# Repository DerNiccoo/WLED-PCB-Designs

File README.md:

# WLED-PCB-Designs
Collection of my WLED PCB Controllers and Boards. They are not perfect, they are not the best, but I tried.

Main Constraints are 1oz copper with 2 layer and 100x100 maximum size to still get the cheap PCB manufacture prices.

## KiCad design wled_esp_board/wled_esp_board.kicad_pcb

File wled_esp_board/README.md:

# WLED ESP32-S3 Controller Board

A compact, low-idle-power ESP32-S3 development board designed as a drop-in controller for WLED-driven LED installations. The board accepts both 5V via pin headers and USB-C (USB 2.0), exposes the full ESP32-S3 GPIO pinout on standard 2.54 mm headers, and deliberately omits an LDO regulator in favor of a switching buck converter to minimize idle power draw.

## Overview

This board was created because I wanted to create my own dev board with the focus on low power consumption even in idle.

## Motivation & Design Decisions

- **Buck converter instead of LDO**: The AP63203WU is a 2A synchronous step-down regulator. Compared to a classic AMS1117/ME6211-style LDO, it wastes virtually no power as heat at light loads, making it ideal for always-on WLED setups.
- **USB-C (USB 2.0, 16-pin)**: Full USB-C receptacle with proper CC resistors (R2/R3, 5.1 kΩ) for correct 5V/500mA enumeration and ESD protection via USBLC6-2SC6.
- **Schottky reverse-polarity diode (D1, SS34)**: Protects the board when power is fed through the 5V pin headers. 3A continuous rating with low forward voltage to minimize drop.
- **Polyfuse (F1)**: Resettable 1A/30V PTC fuse on the USB path for short-circuit protection — no need to replace fuses after a mishap.
- **Reset + Boot buttons**: Physical access to BOOT and RESET for easy firmware flashing without needing any external tool.
- **Easy iron solderable**: 5 small 1mm pins to access as better access to solder the backside of the ESP without the need of a heatgun or hotplate

## Pinout

The board breaks out all ESP32-S3-WROOM-1 GPIOs across four 9-pin 2.54 mm headers (J1–J4). Power rails (5V and 3.3V) are available directly on the headers.

## Schematic

## PCB Layout

***

## Bill of Materials

> LCSC links point to the exact parts used. Where no LCSC link is listed, the part is a generic 0805 passive available from any supplier.

| Ref | Qty | Value / Part | Package | Key Specs | LCSC |
|-----|-----|-------------|---------|-----------|------|
| U1 | 1 | ESP32-S3-WROOM-1 | SMD 25.5×18 mm | Xtensa LX7 dual-core, 2.4 GHz Wi-Fi + BT5, 16 MB flash, 8 MB PSRAM | [C2913202](https://www.lcsc.com/product-detail/C2913202.html) |
| U2 | 1 | USBLC6-2SC6 | SOT-23-6 | ESD protection, 17V clamp, 5A Ipp — guards USB-C data lines | [C7519](https://www.lcsc.com/product-detail/C7519.html) |
| U3 | 1 | AP63203WU | TSOT-23-6 | 2A sync buck, 3.3V fixed output, 1.1 MHz, no LDO heat waste | [C780769](https://www.lcsc.com/product-detail/C780769.html) |
| L1 | 1 | 4.7 µH | 1210 | 2.5A / 3.1A saturation, 115 mΩ DCR — buck converter output inductor | [C48945753](https://www.lcsc.com/product-detail/C48945753.html) |
| D1 | 1 | SS34 | SMA (DO-214AC) | 40V / 3A Schottky, reverse-polarity protection on 5V pin rail | [C8678](https://www.lcsc.com/product-detail/C8678.html) |
| F1 | 1 | Polyfuse 1A | 1206 | PTC resettable fuse 30V / 1A — USB input overcurrent protection | [C5358568](https://www.lcsc.com/product-detail/C5358568.html) |
| J2 | 1 | USB-C Receptacle | HRO TYPE-C-31-M-12 | USB 2.0, 16-pin, through-hole reinforced | — |
| J1,J3,J4,J5 | 4 | 1×9 Pin Header | 2.54 mm | GPIO breakout headers | [C41430882](https://www.lcsc.com/product-detail/C41430882.html) |
| C1,C3,C6,C9 | 4 | 100 nF | 0805 | Decoupling caps for power rails | — |
| C2,C7,C8 | 3 | 22 µF | 0805 | Bulk capacitance, X5R ceramic 6.3V | [C307530](https://www.lcsc.com/product-detail/C307530.html) |
| C5 | 1 | 10 µF | 0805 | Buck output filter capacitor | — |
| R1 | 1 | 10 kΩ | 0805 | Pull-up resistor | — |
| R2,R3 | 2 | 5.1 kΩ | 0805 | USB-C CC pull-down resistors (required for correct 5V/500mA enumeration) | — |
| R4,R5 | 2 | 22 Ω | 0805 | USB D+/D− series termination resistors | — |
| SW1 | 1 | Reset | 5.2×5.2 mm SMD tact | Hardware reset | — |
| SW2 | 1 | Boot | 5.2×5.2 mm SMD tact | Puts ESP32-S3 into download mode | — |

***

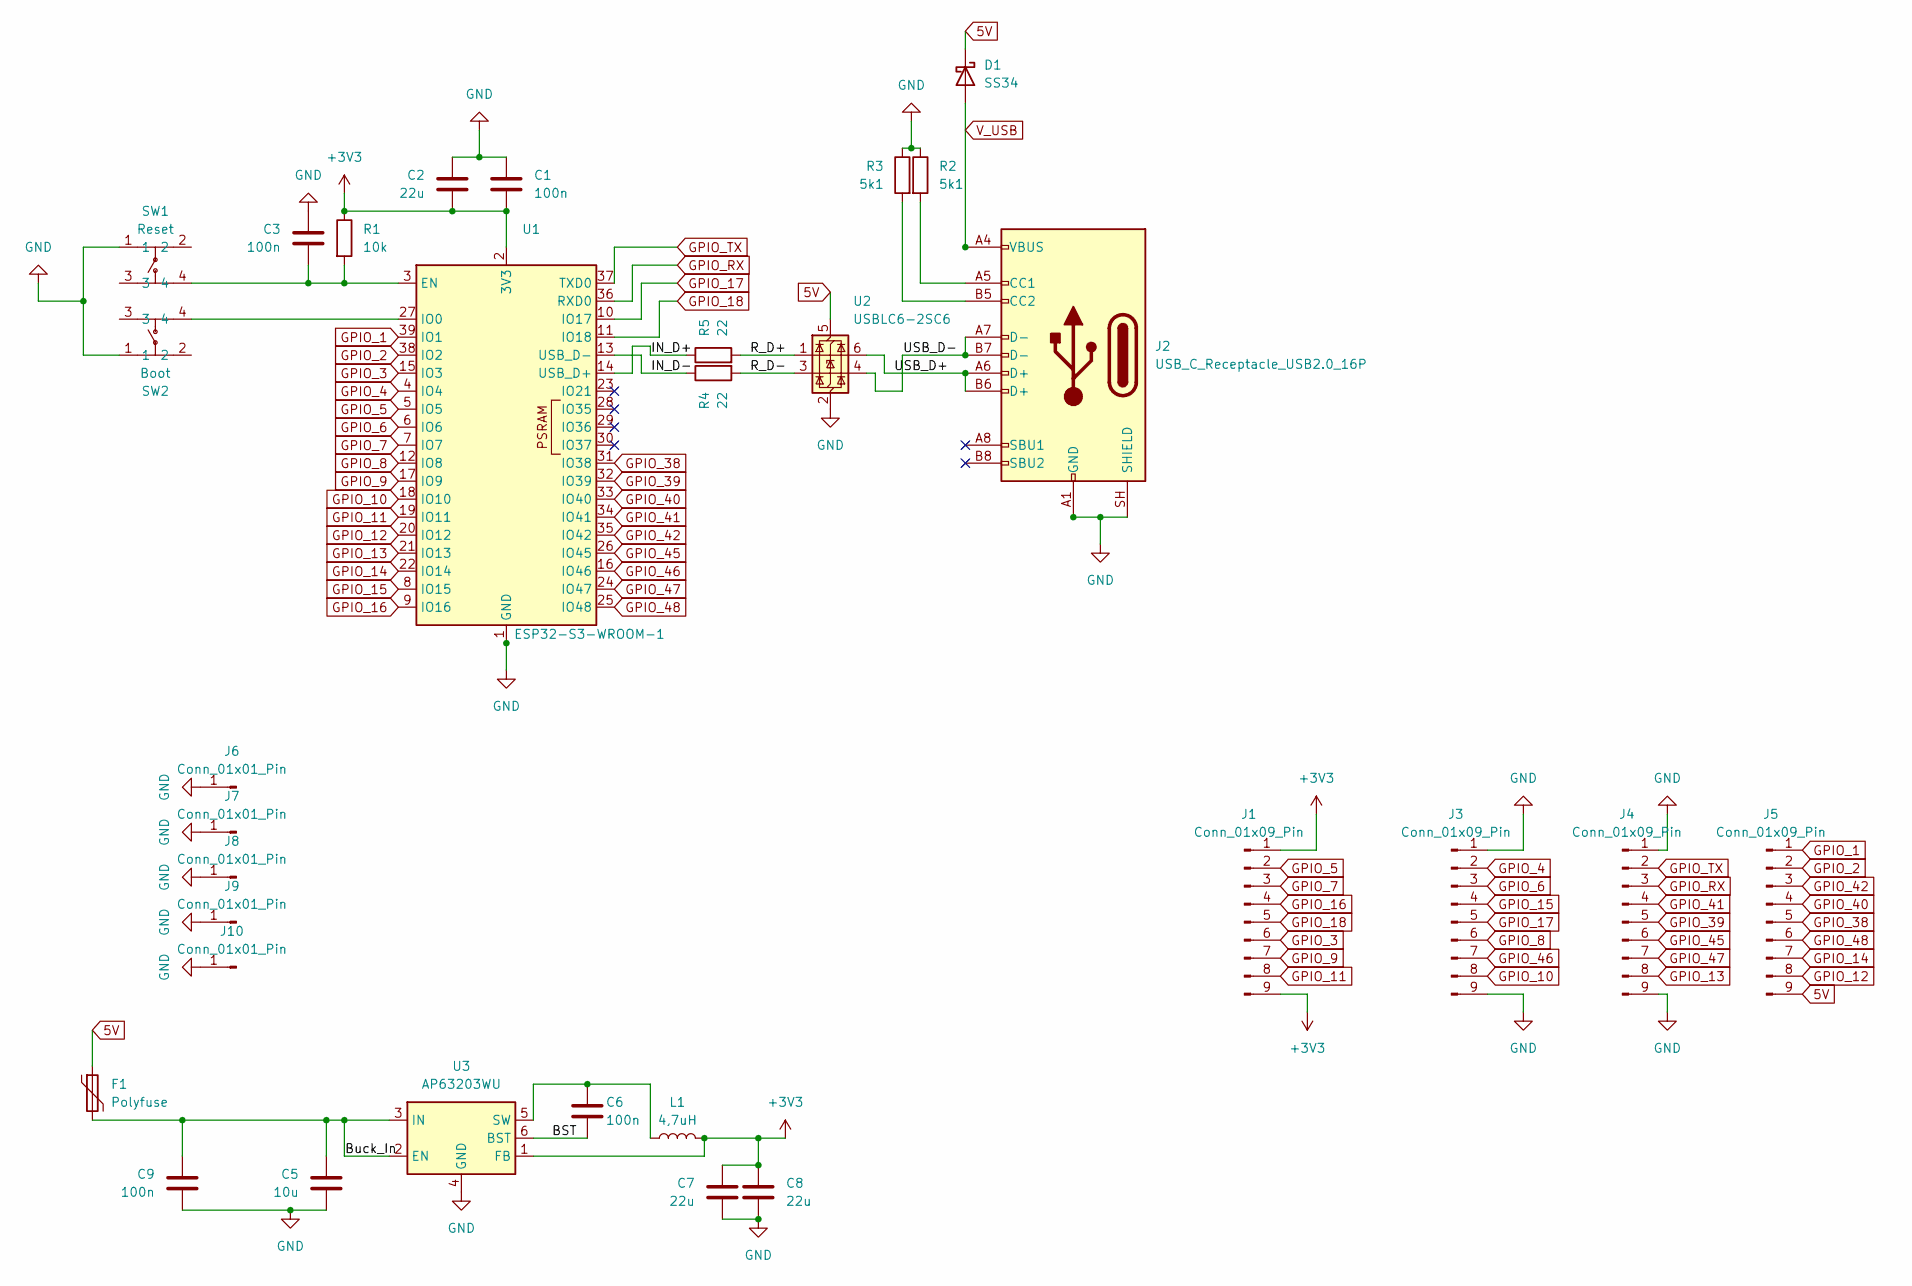
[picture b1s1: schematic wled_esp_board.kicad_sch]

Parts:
C1, C3, C6, C9: 100n; C_0805_2012Metric_Pad1.18x1.45mm_HandSolder
C2, C7, C8: 22u; C_0805_2012Metric_Pad1.18x1.45mm_HandSolder
C5: 10u; C_0805_2012Metric_Pad1.18x1.45mm_HandSolder
D1: SS34; D_SMA_Handsoldering
F1: Polyfuse; Fuse_1206_3216Metric_Pad1.42x1.75mm_HandSolder
J1, J3, J4, J5: Conn_01x09_Pin; PinHeader_1x09_P2.54mm_Vertical
J2: USB_C_Receptacle_USB2.0_16P; USB_C_Receptacle_HRO_TYPE-C-31-M-12
J6, J7, J8, J9, J10: Conn_01x01_Pin; PinHeader_1x01_P1.00mm_Horizontal
L1: 4,7uH; L_1210_3225Metric_Pad1.42x2.65mm_HandSolder
R1: 10k; R_0805_2012Metric_Pad1.20x1.40mm_HandSolder
R2, R3: 5k1; R_0805_2012Metric_Pad1.20x1.40mm_HandSolder
R4, R5: 22; R_0805_2012Metric_Pad1.20x1.40mm_HandSolder
SW1: Reset; SW-SMD_4P-L5.2-W5.2-P3.70-LS6.4; LCSC Part C36936641
SW2: Boot; SW-SMD_4P-L5.2-W5.2-P3.70-LS6.4; LCSC Part C36936641
U1: ESP32-S3-WROOM-1
U2: USBLC6-2SC6; SOT-23-6_Handsoldering
U3: AP63203WU; TSOT-23-6_HandSoldering

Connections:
5V: D1.1 (K), F1.1, J5.9, U2.5 (VBUS)
+3V3: C1.2, C2.1, C7.1, C8.1, J1.1, J1.9, L1.2, R1.1, U1.2 (3V3), U3.1 (FB)
/BST: C6.2, U3.6 (BST)
/Buck_In: C5.1, C9.1, F1.2, U3.2 (EN), U3.3 (IN)
/IN_D+: R5.1, U1.14 (USB_D+)
/IN_D-: R4.1, U1.13 (USB_D-)
/R_D+: R5.2, U2.1 (I/O1)
/R_D-: R4.2, U2.3 (I/O2)
/USB_D+: J2.A6 (D+), J2.B6 (D+), U2.6 (I/O1)
/USB_D-: J2.A7 (D-), J2.B7 (D-), U2.4 (I/O2)
GND: C1.1, C2.2, C3.1, C5.2, C7.2, C8.2, C9.2, J2.A1 (GND), J2.A12 (GND), J2.B1 (GND), J2.B12 (GND), J2.SH (SHIELD), J3.1, J3.9, J4.1, J4.9, J6.1 (Pin_1_1), J7.1 (Pin_1_1), J8.1 (Pin_1_1), J9.1 (Pin_1_1), J10.1 (Pin_1_1), R2.1, R3.1, SW1.1, SW2.1, U1.1 (GND), U1.40 (GND), U1.41 (GND), U2.2 (GND), U3.4 (GND)
GPIO_1: J5.1, U1.39 (IO1)
GPIO_2: J5.2, U1.38 (IO2)
GPIO_3: J1.6, U1.15 (IO3)
GPIO_4: J3.2, U1.4 (IO4)
GPIO_5: J1.2, U1.5 (IO5)
GPIO_6: J3.3, U1.6 (IO6)
GPIO_7: J1.3, U1.7 (IO7)
GPIO_8: J3.6, U1.12 (IO8)
GPIO_9: J1.7, U1.17 (IO9)
GPIO_10: J3.8, U1.18 (IO10)
GPIO_11: J1.8, U1.19 (IO11)
GPIO_12: J5.8, U1.20 (IO12)
GPIO_13: J4.8, U1.21 (IO13)
GPIO_14: J5.7, U1.22 (IO14)
GPIO_15: J3.4, U1.8 (IO15)
GPIO_16: J1.4, U1.9 (IO16)
GPIO_17: J3.5, U1.10 (IO17)
GPIO_18: J1.5, U1.11 (IO18)
GPIO_38: J5.5, U1.31 (IO38)
GPIO_39: J4.5, U1.32 (IO39)
GPIO_40: J5.4, U1.33 (IO40)
GPIO_41: J4.4, U1.34 (IO41)
GPIO_42: J5.3, U1.35 (IO42)
GPIO_45: J4.6, U1.26 (IO45)
GPIO_46: J3.7, U1.16 (IO46)
GPIO_47: J4.7, U1.24 (IO47)
GPIO_48: J5.6, U1.25 (IO48)
GPIO_RX: J4.3, U1.36 (RXD0)
GPIO_TX: J4.2, U1.37 (TXD0)
unnamed: J2.A5 (CC1), R2.2
unnamed: J2.B5 (CC2), R3.2
unnamed: C3.2, R1.2, SW1.4, U1.3 (EN)
unnamed: SW2.4, U1.27 (IO0)
unnamed: C6.1, L1.1, U3.5 (SW)
V_USB: D1.2 (A), J2.A4 (VBUS), J2.A9 (VBUS), J2.B4 (VBUS), J2.B9 (VBUS)

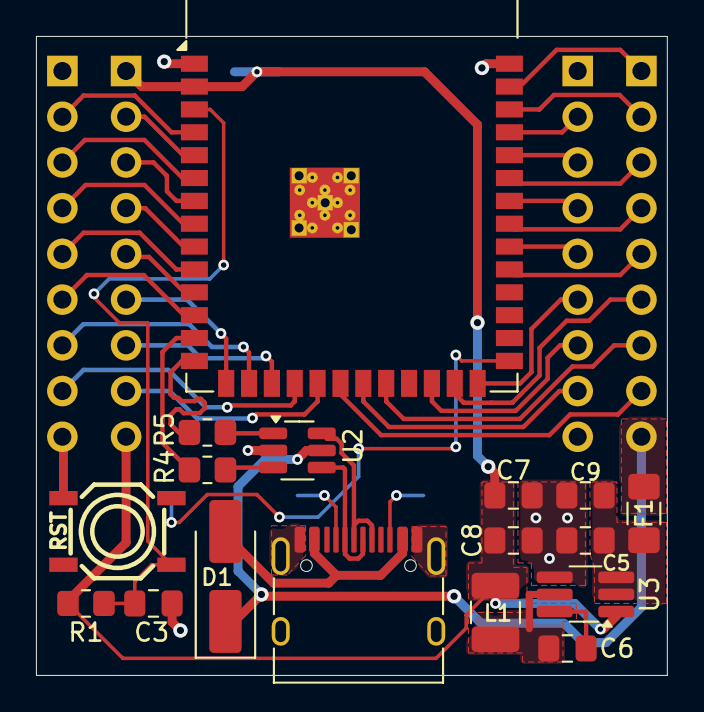
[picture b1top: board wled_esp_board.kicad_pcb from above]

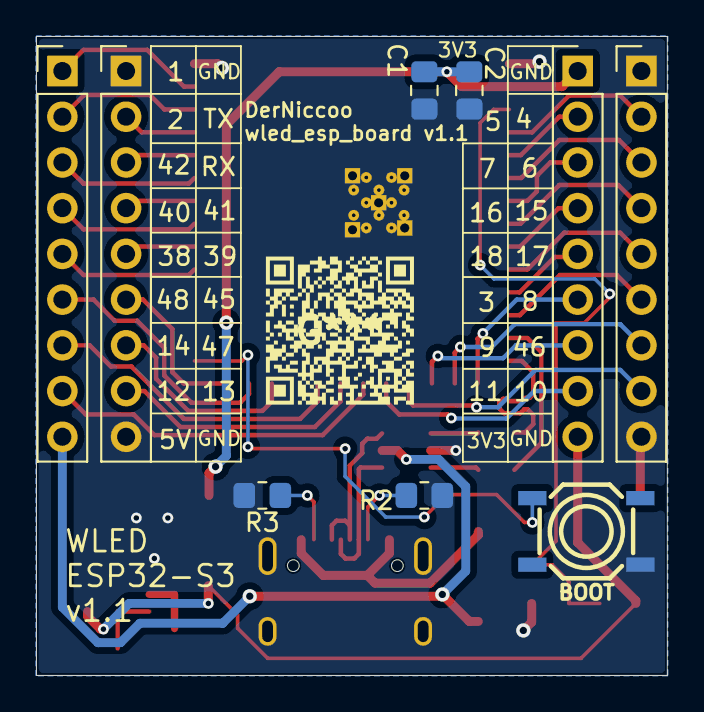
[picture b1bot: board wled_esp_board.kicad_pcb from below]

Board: 2 copper layers, 35.0 x 35.5 mm, 31 parts (9 on the bottom side), 46 nets.

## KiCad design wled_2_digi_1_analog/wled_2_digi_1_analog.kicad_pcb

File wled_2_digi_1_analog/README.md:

# WLED LED Controller Board

A 4-channel WLED controller board built around the custom [ESP32-S3 dev board](../wled_esp_board/README.md). It supports **two digital LED strips** (e.g. WS2812B / SK6812 via level-shifted data lines) and **one analog/PWM-dimmed strip** (5-channel RGBWW), with individually fused power lines per strip output. Total sustained current capacity is ~10A, with 3–4A recommended per strip.

## Overview

This board was designed to be a clean, self-contained controller unit. It plugs the ESP32-S3 board into a socket, handles all power routing, level shifting, MOSFET switching, and fusing in one place. Two power inputs are available, but only **one should be active at a time** — a Schottky diode (D2) and TVS diode (D1) protect the board when switching sources.

## Motivation & Design Decisions

- **Two power inputs, one at a time**: A 5.5×2.1 mm barrel jack (J1) and a screw terminal input are both present for flexibility (bench supply vs. PSU). The Schottky diode D2 (SS34) on one path prevents backfeed between sources.
- **TVS protection (D1, SMBJ26A)**: A 26V transient voltage suppressor clamps voltage spikes on the main 5V bus — important with longer LED strip wiring that can generate inductive kickback.
- **Individually fused power lines**: Each LED strip's 5V supply line runs through a dedicated ATO blade fuse holder (FH2/FH3/FH4). This isolates fault conditions to a single channel. ATO fuses are cheap, universally available, and hot-swappable.
- **Level shifter (U1, 74AHCT125)**: The ESP32-S3 runs at 3.3V. WS2812B and similar LEDs expect 5V logic. The 74AHCT125 quad buffer shifts both DATA lines and clock signals to proper 5V levels reliably, without needing a dedicated 3.3V-compatible LED strip.
- **N-channel MOSFETs for PWM dimming (Q1, Q6–Q9, IRLR7843TR)**: Five low-side N-channel MOSFETs handle the analog RGBWW channels. The IRLR7843TR has an extremely low RDS(on) (< 3 mΩ), so it barely heats up even at 3–4A per channel.
- **P-channel MOSFETs for high-side switching (Q2, Q5)**: High-side switches on the digital strip power rails, driven by NPN transistors (Q3/Q4, MMBT4401). This allows the ESP32-S3 to cut power to strips entirely, useful for preventing LED ghost-lighting when WLED is in an "off" state.
- **5V buck for board logic (U2, AP63205WU)**: Derives a clean regulated 5V from the main bus specifically for the 74AHCT125 and the ESP32-S3 board's own regulator input. Uses a 4.7 µH / 1210 inductor (L1) on the switching output.
- **Screw terminals in 2- and 3-pin configurations**: Instead of using hard-to-find 1- or 5-pin terminals, standard KF301 2-pin, 3-pin and 4-pin blocks (5.0 mm pitch) are used throughout.

## ESP32-S3 Pinout (Signal Mapping)

The controller board uses the following signals from the ESP32-S3 board headers:

### Digital LED Strip Signals

| Signal | ESP32-S3 GPIO | Description |
|--------|--------------|-------------|
| DATA1 | IO_16 | Digital data line — Strip 1 (e.g. WS2812B) |
| DATA2 | IO_18 | Digital data line — Strip 2 |
| CLK1 | IO_15 | Clock — Strip 1 (for SPI-based LEDs like APA102) |
| CLK2 | IO_17 | Clock — Strip 2 |
| HS_Enabled_1 | IO_6 | High-side enable — cuts 5V to Strip 1 |
| HS_Enabled_2 | IO_7 | High-side enable — cuts 5V to Strip 2 |

### Analog / PWM Strip Signals

| Signal | ESP32-S3 GPIO | Description |
|--------|--------------|-------------|
| A_CH1 | IO_11 | PWM channel 1 (e.g. Red) |
| A_CH2 | IO_12 | PWM channel 2 (e.g. Green) |
| A_CH3 | IO_9 | PWM channel 3 (e.g. Blue) |
| A_CH4 | IO_5 | PWM channel 4 (e.g. Warm White) |
| A_CH5 | IO_4 | PWM channel 5 (e.g. Cold White) |

## Schematic

## PCB Layout

***

## Bill of Materials

> LCSC links point to the exact parts used. Where no LCSC link is listed, the part is a generic passive available from stock.

| Ref | Qty | Value / Part | Package | Key Specs | LCSC |
|-----|-----|-------------|---------|-----------|------|
| ESP32-S3-Board1 | 1 | WLED ESP32-S3 Board | Custom header socket | See [esp_board README](../wled_esp_board/README.md) | — |
| U1 | 1 | 74AHCT125 | SOIC-14 | Quad 3-state buffer, 5V output — level shifts 3.3V ESP data/clock to 5V | [C554502](https://www.lcsc.com/product-detail/C554502.html) |
| U2 | 1 | AP63205WU | TSOT-23-6 | 2A synchronous buck, 5V fixed — powers logic rail from main bus | [C2071056](https://www.lcsc.com/product-detail/C2071056.html) |
| Q1,Q6–Q9 | 5 | IRLR7843TR (UMW) | TO-252 | N-Ch, 30V, 161A rated, <3 mΩ RDS(on) — analog PWM low-side switches | [C7499399](https://www.lcsc.com/product-detail/C7499399.html) |
| Q2,Q5 | 2 | AO4407A (or equiv.) | SOIC-8 | P-Ch, 30V, 12A — high-side power switch for digital strips | [C16072](https://www.lcsc.com/product-detail/C16072.html) |
| Q3,Q4 | 2 | MMBT4401LT1G | SOT-23 | NPN, 40V / 600mA — drives gate of P-Ch MOSFETs from 3.3V GPIO | [C31776](https://www.lcsc.com/product-detail/C31776.html) |
| D1 | 1 | SMBJ26A | SMB (DO-214AA) | 26V TVS, 14.25A Ipp — bus transient suppression | [C19077580](https://www.lcsc.com/product-detail/C19077580.html) |
| D2 | 1 | SS34 | SMA (DO-214AC) | 40V / 3A Schottky — reverse-polarity / backfeed protection | [C8678](https://www.lcsc.com/product-detail/C8678.html) |
| FH2,FH3,FH4 | 3 | ATO Fuse Holder | Through-hole clip | One per strip power line — accepts standard ATO blade fuses | [C717032](https://www.lcsc.com/product-detail/C717032.html) |
| L1 | 1 | 4.7 µH | 1210 | 2.5A / 3.1A saturation, 115 mΩ DCR — buck output inductor | [C48945753](https://www.lcsc.com/product-detail/C48945753.html) |
| C1 | 1 | 470 µF / 35V | Radial D10mm | Electrolytic bulk cap — main bus reservoir | [C106703](https://www.lcsc.com/product-detail/C106703.html) |
| C3 | 1 | 10 µF | 0805 | Buck output filter | — |
| C4,C6,C7 | 3 | 100 nF | 0805 | Decoupling caps | — |
| C8,C9 | 2 | 22 µF | 0805 | Ceramic X5R 6.3V — local bulk caps | [C307530](https://www.lcsc.com/product-detail/C307530.html) |
| J1 | 1 | Barrel Jack 5.5/2.1 mm | Horizontal THT | Primary power input (center positive) | — |
| J2 | 1 | Screw Terminal 3-pin | KF301 5.0 mm | Secondary / alternative power input + GND | — |
| J3,J4 | 2 | Screw Terminal 4-pin | KF301 5.0 mm | LED strip output connectors (2× split 4-pin instead of 8-pin) | — |
| U3–U5 | 3 | Screw Terminal 2-pin | KF301 5.0 mm | Analog strip channel outputs | — |
| R2,R7,R11,R13,R15,R17,R19 | 7 | 100 kΩ | 0805 | Gate pull-down / bias resistors | [C149504](https://www.lcsc.com/product-detail/C149504.html) |
| R3,R6 | 2 | 1 kΩ | 0805 | NPN base resistors | — |
| R4,R5,R8,R9 | 4 | 33 Ω | 0805 | Signal series termination (level shifter outputs) | [C17634](https://www.lcsc.com/product-detail/C17634.html) |
| R10,R12,R14,R16,R18 | 5 | 10 Ω | 0805 | Gate resistors for N-Ch MOSFETs | [C17415](https://www.lcsc.com/product-detail/C17415.html) |

***

## Power Budget

| Source | Max Recommended | Notes |
|--------|----------------|-------|
| Total board input | 10A | Limited by wiring and screw terminal rating |
| Per digital strip | 3–4A | Fused individually at FH2/FH3 |
| Analog strip per channel | 3–4A | Fused at FH4; 5 channels share one fuse |

> Always size your ATO fuses to the **strip's** maximum draw, not the board's maximum. A 3A fuse per digital strip and a 5A fuse for the analog strip are good starting points.

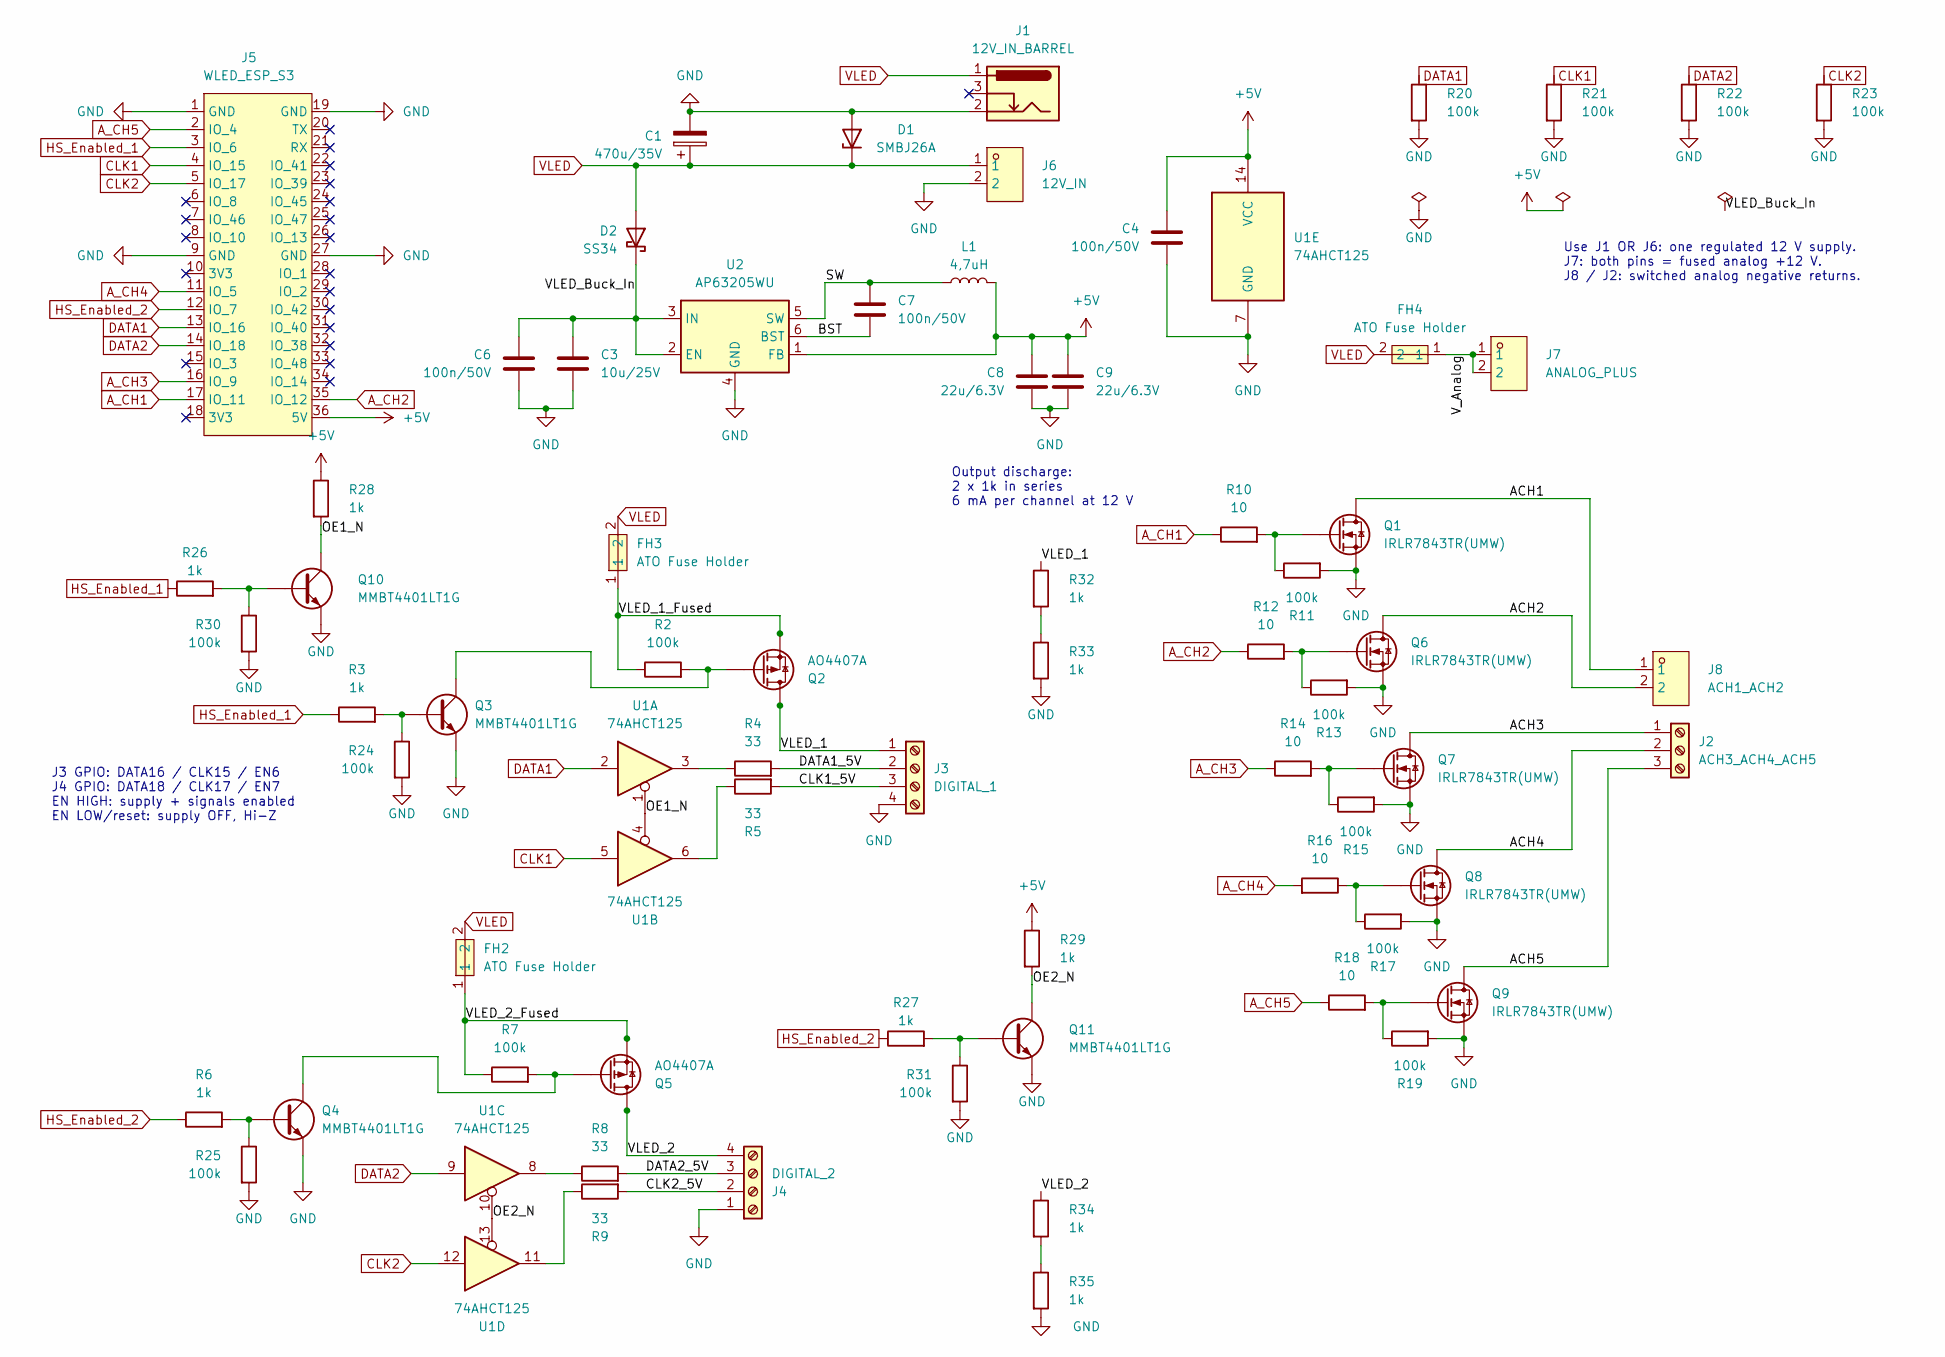
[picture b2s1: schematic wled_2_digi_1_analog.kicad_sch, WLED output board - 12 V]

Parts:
C1: 470u/35V; CP_Radial_D10.0mm_P5.00mm
C3: 10u/25V; C_0805_2012Metric_Pad1.18x1.45mm_HandSolder; Voltage 25V; MPN CL21A106KAYNNNE; LCSC C15850
C4, C6, C7: 100n/50V; C_0805_2012Metric_Pad1.18x1.45mm_HandSolder; Voltage 50V; MPN CL21B104KBCNNNC; LCSC C1711
C8, C9: 22u/6.3V; C_0805_2012Metric_Pad1.18x1.45mm_HandSolder
D1: SMBJ26A; D_SMB_Handsoldering
D2: SS34; D_SMA_Handsoldering
FH2, FH3, FH4: ATO Fuse Holder; FUSE-TH_XF-101; LCSC Part C717032
J1: 12V_IN_BARREL; BarrelJack_Horizontal
J2: ACH3_ACH4_ACH5; CONN-TH_P5.00_KF301-5.0-3P
J3: DIGITAL_1; CONN-TH_P5.00_KF301-5.0-4P
J4: DIGITAL_2; CONN-TH_P5.00_KF301-5.0-4P
J5: WLED_ESP_S3
J6: 12V_IN; CONN-TH_P5.00_KF301-5.0-2P; LCSC Part C474881
J7: ANALOG_PLUS; CONN-TH_P5.00_KF301-5.0-2P; LCSC Part C474881
J8: ACH1_ACH2; CONN-TH_P5.00_KF301-5.0-2P; LCSC Part C474881
L1: 4,7uH; L_1210_3225Metric_Pad1.42x2.65mm_HandSolder
Q1, Q6, Q7, Q8, Q9: IRLR7843TR(UMW); TO-252-2
Q2, Q5: AO4407A; SO-8_3.9x4.9mm_P1.27mm; MPN AO4407A
Q3, Q4: MMBT4401LT1G; SOT-23
Q10, Q11: MMBT4401LT1G; SOT-23; MPN MMBT4401LT1G; LCSC C31776
R2, R7, R11, R13, R15, R17, R19: 100k; R_0805_2012Metric_Pad1.20x1.40mm_HandSolder
R3, R6, R26, R27, R28, R29, R32, R33, R34, R35: 1k; R_0805_2012Metric_Pad1.20x1.40mm_HandSolder
R4, R5, R8, R9: 33; R_0805_2012Metric_Pad1.20x1.40mm_HandSolder
R10, R12, R14, R16, R18: 10; R_0805_2012Metric_Pad1.20x1.40mm_HandSolder
R20, R21, R22, R23, R24, R25, R30, R31: 100k; R_0805_2012Metric_Pad1.20x1.40mm_HandSolder; Tolerance 1%; LCSC C149504
U1: 74AHCT125; SOIC-14_3.9x8.7mm_P1.27mm
U2: AP63205WU; TSOT-23-6_HandSoldering

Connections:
+5V: C4.1, C8.1, C9.1, J5.36 (5V), L1.1, R28.1, R29.1, U1.14 (VCC), U2.1 (FB)
/ACH1: J8.1, Q1.2 (D)
/ACH2: J8.2, Q6.2 (D)
/ACH3: J2.1, Q7.2 (D)
/ACH4: J2.2, Q8.2 (D)
/ACH5: J2.3, Q9.2 (D)
/BST: C7.2, U2.6 (BST)
/CLK1_5V: J3.3, R5.2
/CLK2_5V: J4.2, R9.2
/DATA1_5V: J3.2, R4.2
/DATA2_5V: J4.3, R8.2
/OE1_N: Q10.3 (C), R28.2, U1.1, U1.4
/OE2_N: Q11.3 (C), R29.2, U1.10, U1.13
/SW: C7.1, L1.2, U2.5 (SW)
/VLED_1: J3.1, Q2.5 (D), Q2.6 (D), Q2.7 (D), Q2.8 (D), R32.1
/VLED_1_Fused: FH3.1, Q2.1 (S), Q2.2 (S), Q2.3 (S), R2.1
/VLED_2: J4.4, Q5.5 (D), Q5.6 (D), Q5.7 (D), Q5.8 (D), R34.1
/VLED_2_Fused: FH2.1, Q5.1 (S), Q5.2 (S), Q5.3 (S), R7.1
/VLED_Buck_In: C3.1, C6.1, D2.1 (K), U2.2 (EN), U2.3 (IN)
/V_Analog: FH4.1, J7.1, J7.2
A_CH1: J5.17 (IO_11), R10.1
A_CH2: J5.35 (IO_12), R12.1
A_CH3: J5.16 (IO_9), R14.1
A_CH4: J5.11 (IO_5), R16.2
A_CH5: J5.2 (IO_4), R18.1
CLK1: J5.4 (IO_15), R21.1, U1.5
CLK2: J5.5 (IO_17), R23.1, U1.12
DATA1: J5.13 (IO_16), R20.1, U1.2
DATA2: J5.14 (IO_18), R22.1, U1.9
GND: C1.2, C3.2, C4.2, C6.2, C8.2, C9.2, D1.2 (A2), J1.2, J3.4, J4.1, J5.1 (GND), J5.9 (GND), J5.19 (GND), J5.27 (GND), J6.2, Q1.3 (S), Q3.2 (E), Q4.2 (E), Q6.3 (S), Q7.3 (S), Q8.3 (S), Q9.3 (S), Q10.2 (E), Q11.2 (E), R11.2, R13.2, R15.2, R17.2, R19.2, R20.2, R21.2, R22.2, R23.2, R24.2, R25.2, R30.2, R31.2, R33.2, R35.2, U1.7 (GND), U2.4 (GND)
HS_Enabled_1: J5.3 (IO_6), R3.1, R26.1
HS_Enabled_2: J5.12 (IO_7), R6.1, R27.1
unnamed: Q1.1 (G), R10.2, R11.1
unnamed: Q2.4 (G), Q3.3 (C), R2.2
unnamed: Q3.1 (B), R3.2, R24.1
unnamed: Q4.1 (B), R6.2, R25.1
unnamed: Q4.3 (C), Q5.4 (G), R7.2
unnamed: Q6.1 (G), R12.2, R13.1
unnamed: Q7.1 (G), R14.2, R15.1
unnamed: Q8.1 (G), R16.1, R17.1
unnamed: Q9.1 (G), R18.2, R19.1
unnamed: Q10.1 (B), R26.2, R30.1
unnamed: Q11.1 (B), R27.2, R31.1
unnamed: R4.1, U1.3
unnamed: R5.1, U1.6
unnamed: R8.1, U1.8
unnamed: R9.1, U1.11
unnamed: R32.2, R33.1
unnamed: R34.2, R35.1
VLED: C1.1, D1.1 (A1), D2.2 (A), FH2.2, FH3.2, FH4.2, J1.1, J6.1

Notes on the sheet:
J3 GPIO: DATA16 / CLK15 / EN6 J4 GPIO: DATA18 / CLK17 / EN7 EN HIGH: supply + signals enabled EN LOW/reset: supply OFF, Hi-Z
Use J1 OR J6: one regulated 12 V supply. J7: both pins = fused analog +12 V. J8 / J2: switched analog negative returns.
Output discharge: 2 x 1k in series 6 mA per channel at 12 V

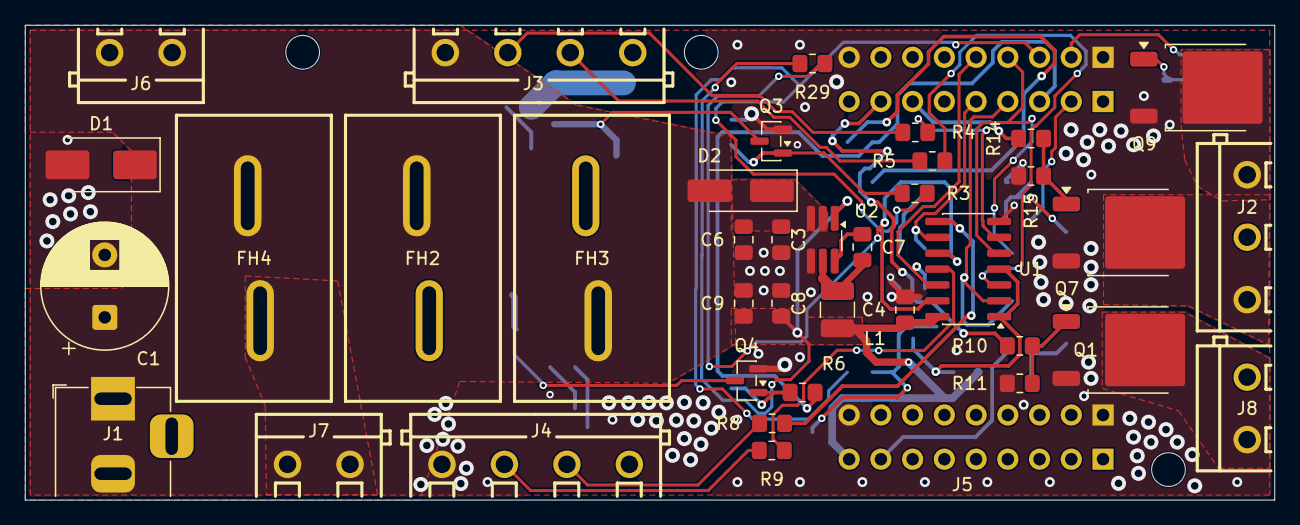
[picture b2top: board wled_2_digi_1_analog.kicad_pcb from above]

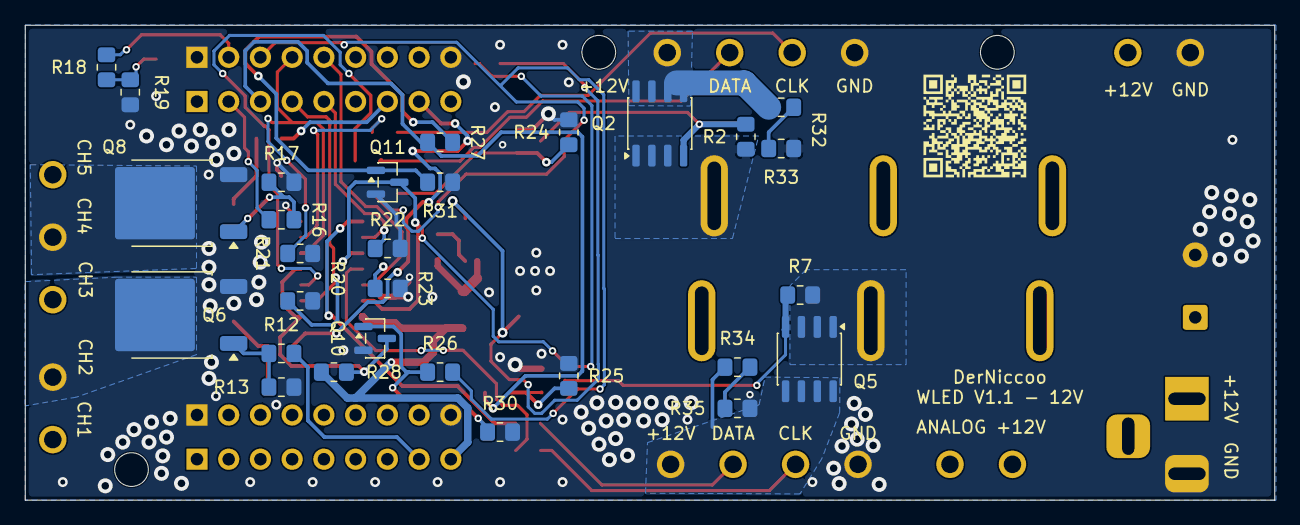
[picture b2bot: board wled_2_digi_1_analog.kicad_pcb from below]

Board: 2 copper layers, 100.0 x 38.0 mm, 71 parts (29 on the bottom side), 50 nets.

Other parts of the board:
H1, H2, H3: (no value)

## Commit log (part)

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2026-05-30 Upload first boards
2026-05-30 Add QR Code
2026-05-30 Moved components closer
2026-05-30 Add 2digi1analog
2026-05-30 Update QR Code
2026-05-31 Update QR Code on base board
2026-05-31 Mounting Holes and 2pin connector
2026-05-31 Switch 5pin to 2+3ping
